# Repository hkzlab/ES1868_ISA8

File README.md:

# ES1868F 8bit ISA Sound Card

## Introduction

This is a sound card for the ISA 8bit bus sporting the **ES1868F** chip by *ESS Technology*.

This chip provides **Sound Blaster PRO 2.0** (stereo), **OPL3** compatibility (via *ESFM*), MPU-401 support and is considered one of the [best chips](https://www.philscomputerlab.com/ess-audiodrive-es1868.html) used in clone cards.

This board provides the following connections:

* Speaker out (amplified)
* Line out
* Line in
* AUX in (internal header, since rev 1.2)
* Microphone in (internal header)
* Joystick port
* MIDI on Joystick port
* Wavetable header
* Volume control header

### Disclaimer

I take NO responsibility for what happens if you decide to build and use this card. Your computer might crash, catch fire or be destroyed in other nasty ways.
You're encourauged to take what you deem fit from this, and use it in your projects!

### Functionalities

✅ means I tested the functionality and it works, ❌ means I tested the functionality and found issues, ? means that the functionality has yet to be tested.

* [✅] FM Synthesis via OPL3 clone (**ESFM**)
* [✅] Digital audio playback
* [✅] Stereo (left/right channel) check (Tested with Sound Blaster PRO Test program, digitized sound mode)
* [✅] Joystick port
* [✅] Speaker Out (amplified)
* [✅] Line out
* [✅] Line in
* [✅] AUX In
* [?] Microphone in
* [✅] MIDI output via Joystick port (tested using DOSMID MPU mode on a Roland SC55)
* [✅] Wavetable daughterboard

The card was tested on:

* [✅] 286 16Mhz / DOS 6.22
* [✅] NEC V20 9.54Mhz / DOS 6.22 (Use **UNISOUND**, see **Configuration** section below)
* [✅] NEC V20 4.77Mhz / DOS 6.22 (Use **UNISOUND**, see **Configuration** section below)
* [✅] 8088 8Mhz / DOS 6.22 (Use **UNISOUND**, see **Configuration** section below)
* [✅] 8088 4.77Mhz / DOS 6.22 (Use **UNISOUND**, see **Configuration** section below)
* [✅] 486DX 40Mhz / DOS 7.1 (Use **UNISOUND**, see **Configuration** section below)
* [✅] Am5x86 40/160Mhz / DOS 7.1 (Use **UNISOUND**, see **Configuration** section below)

## Configuration

This card is jumperless and must be configured before use.
Under DOS you can us the [ESSCFG](software/ESSCFG.EXE) tool and tweak the volume via [ESSVOL](software/ESSVOL.EXE).

The **recommended** way to do this (especially under a very slow machine, like a V20/8088) is by using the [UNISOUND](https://www.vogons.org/viewtopic.php?f=62&t=72553) configurator.

It's important to add the `/XEA` parameter to `UNISOUND.COM` when using it, and remember to execute it after setting the `BLASTER` environment variable, for example with the command `SET BLASTER=A220 I5 D1 P330 T5 J201` (clearly changing the parameters depending on your setup).

**WARNING**: If you use an XT-IDE adapter at the default base address (300h), remember to set the MPU-401 base for this card to something else (like 330h)!

## Bill of Materials

**TODO**

Value of L1/L2/L3 ferrite beads is non critical. I used [these](https://www.mouser.it/ProductDetail/623-2743001112LF).

## Known Issues

### Rev 1.0

* Joystick plug "J3" silkscreen overlaps with some resistors (fixed in 1.1).
* The thread in the audio jacks I'm using (Kycon STX-3100-3CB) is flush with the bracket, so if the bracket has some bending, the plug risks to be pushed away (fixed in 1.1 by moving the connectors 0,5mm towards the edge).

## Credits

Thanks to [Sergey Kiselev](https://github.com/skiselev) for his symbol/footprint library!

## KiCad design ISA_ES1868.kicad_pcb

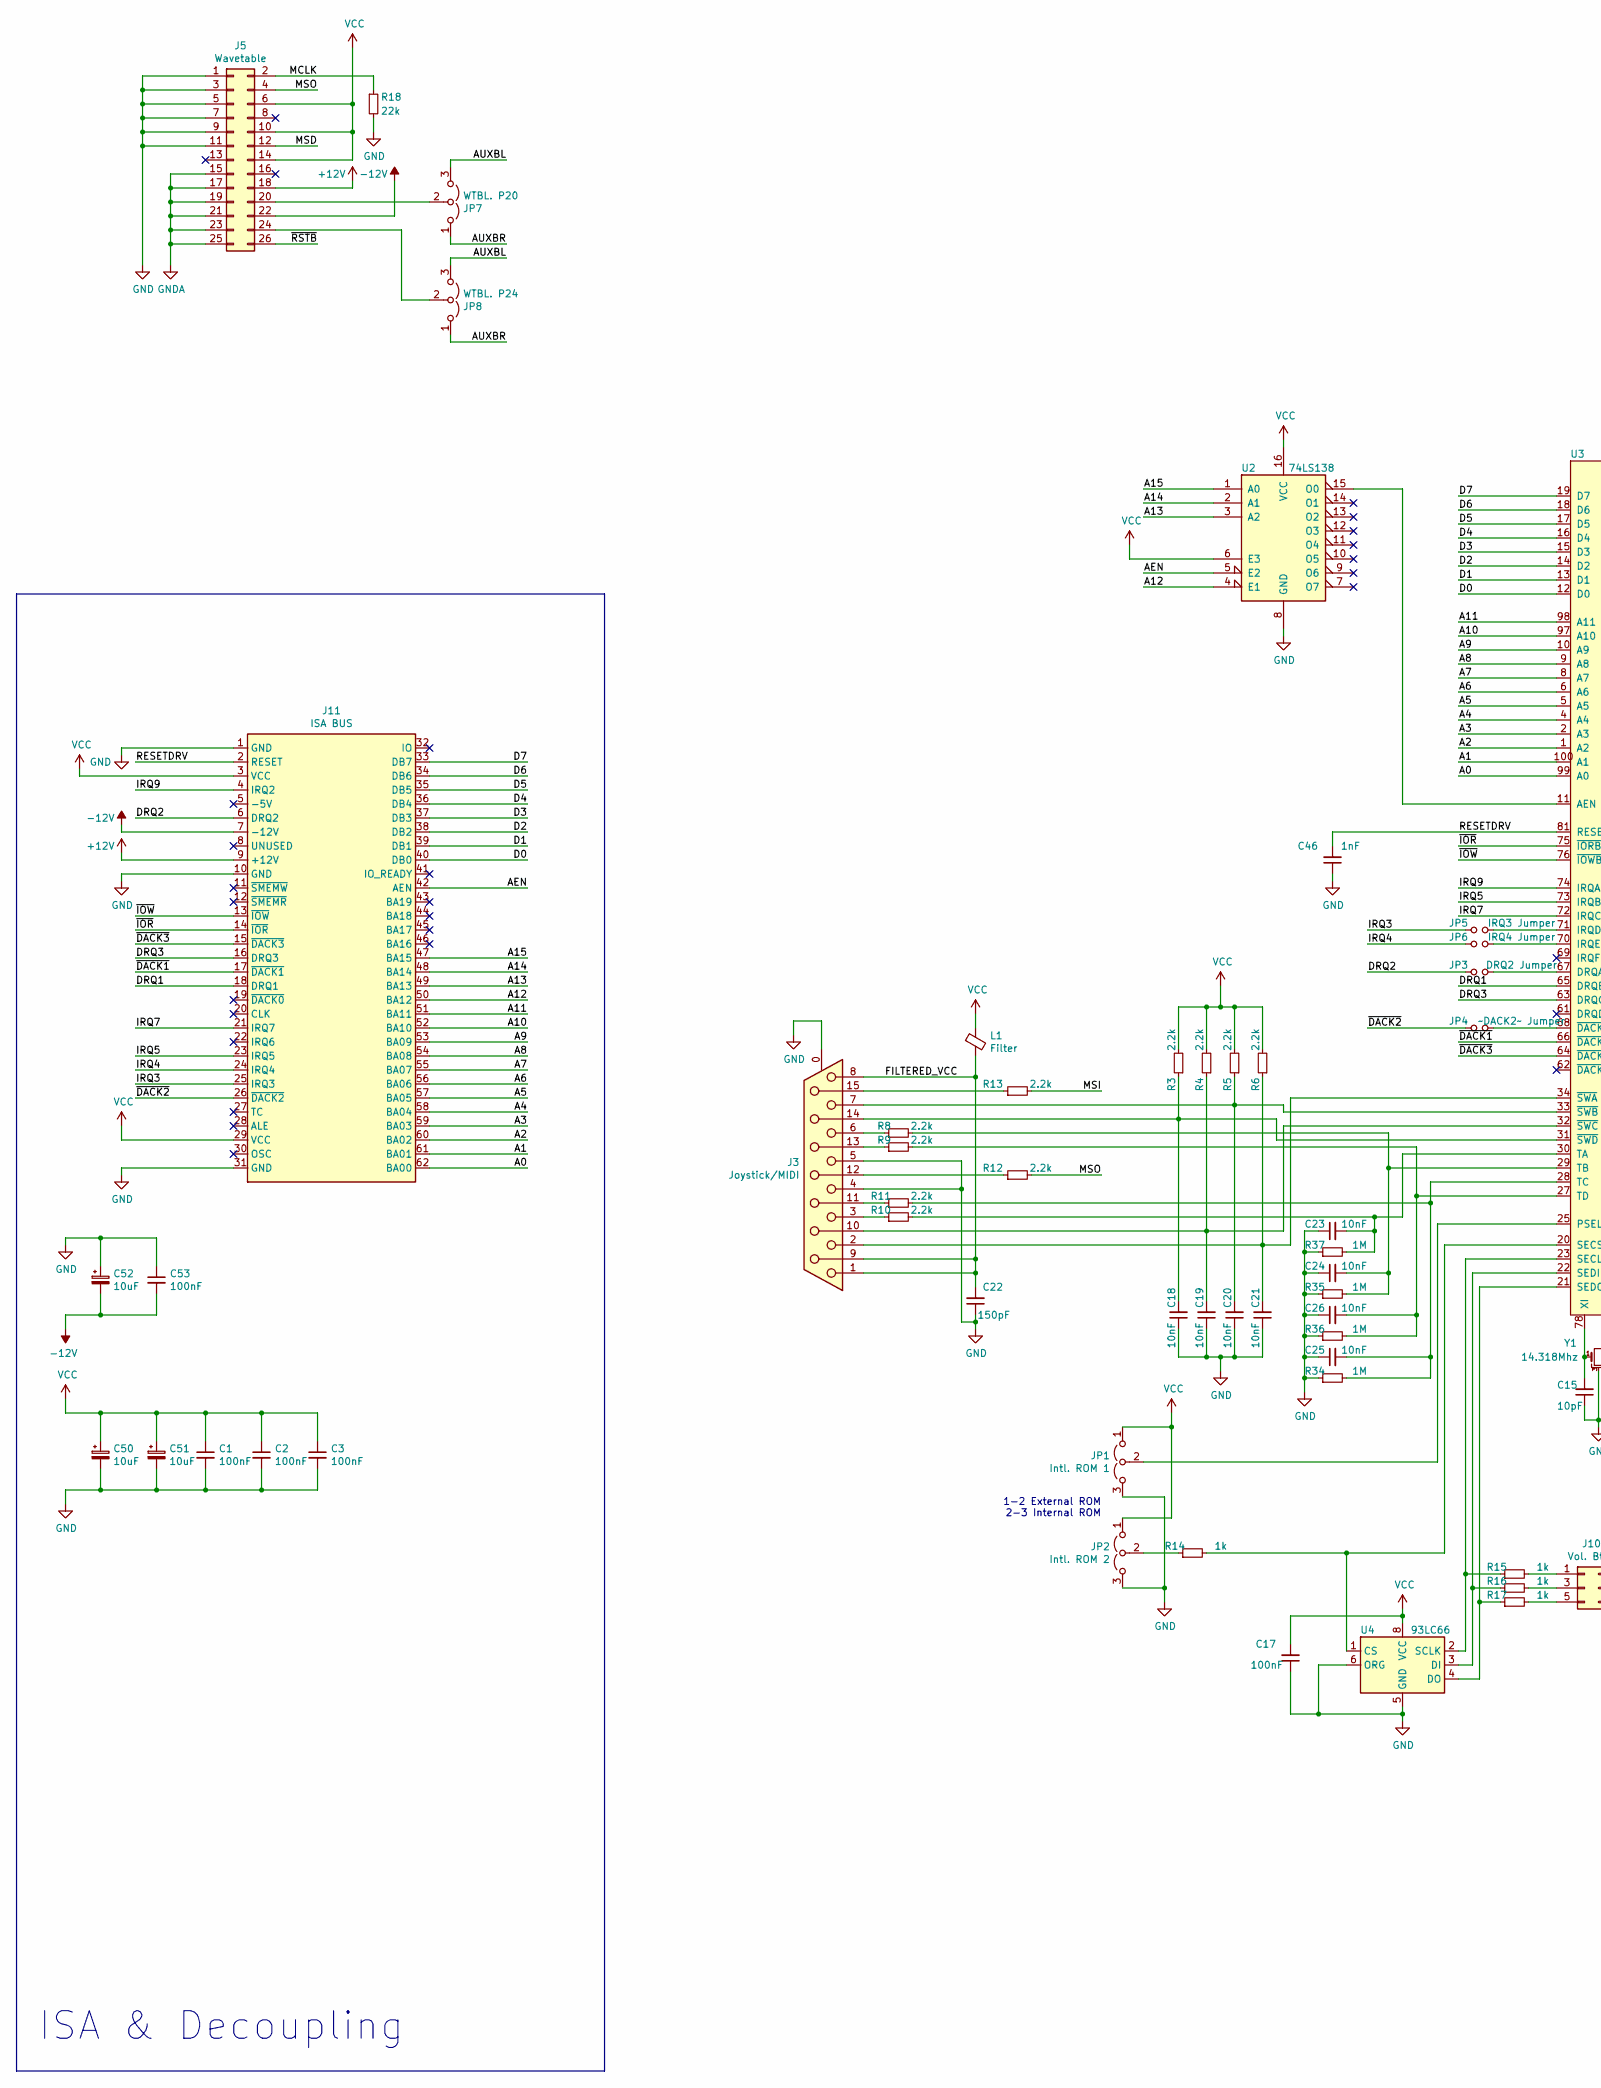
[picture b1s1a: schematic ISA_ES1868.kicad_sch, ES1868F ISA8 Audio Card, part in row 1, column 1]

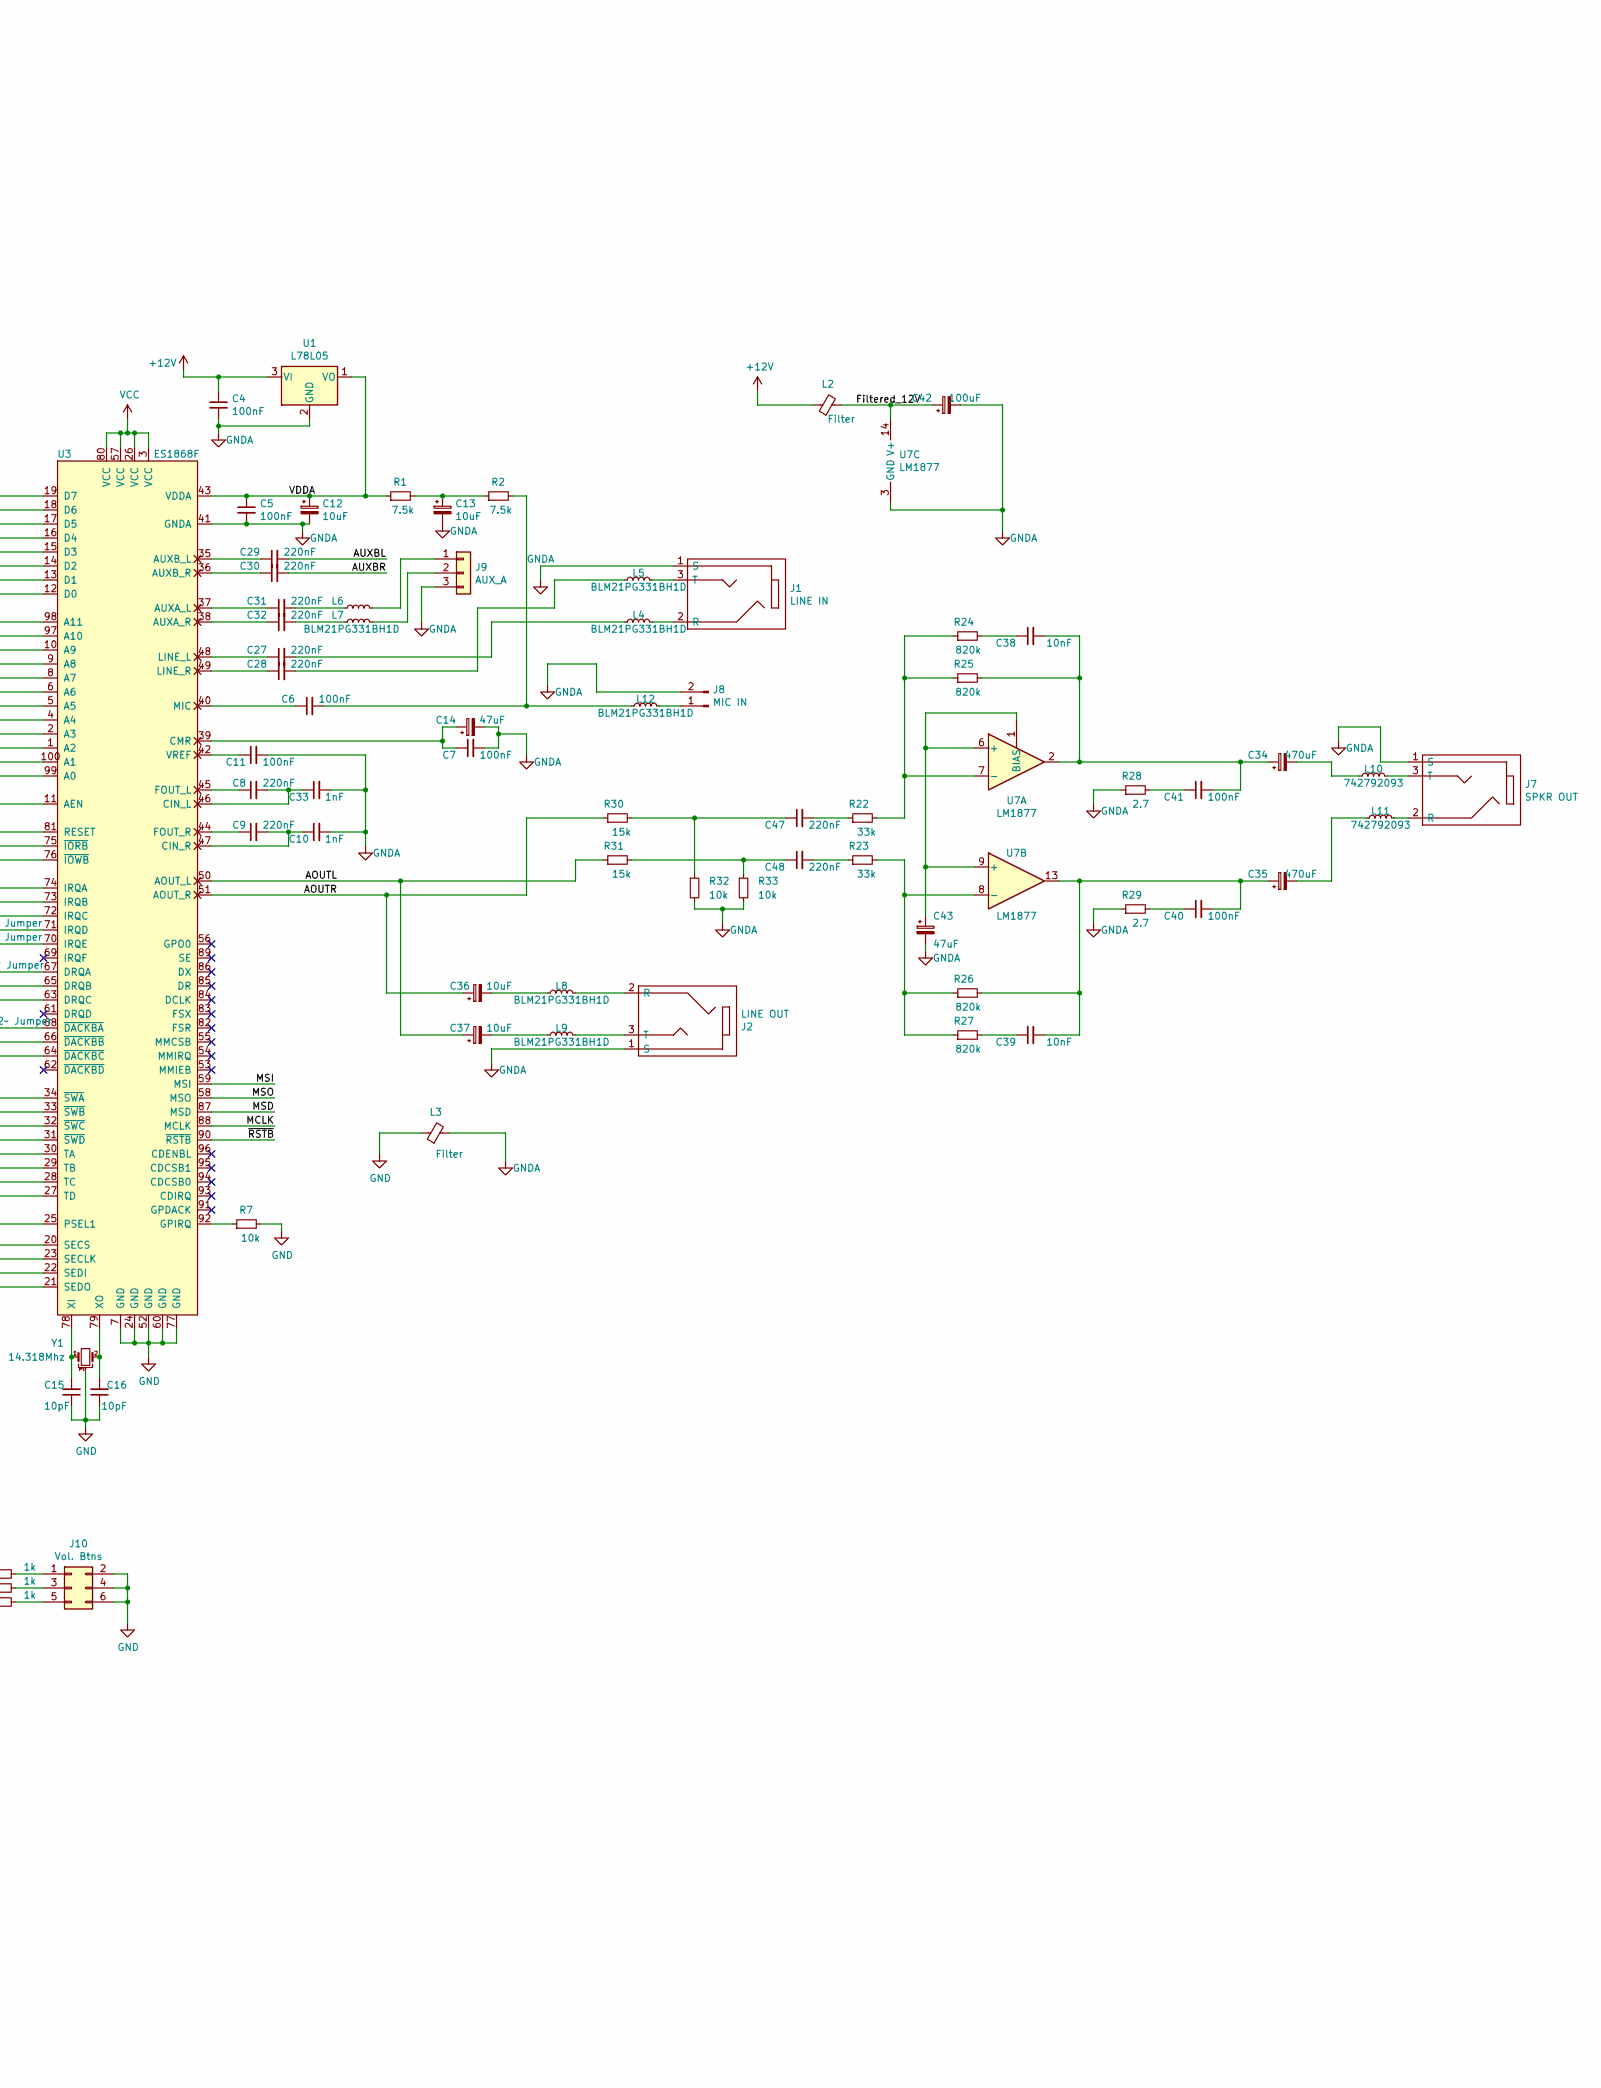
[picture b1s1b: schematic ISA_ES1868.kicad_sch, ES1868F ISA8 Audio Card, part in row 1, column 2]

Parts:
C1, C2, C3, C4, C5, C6, C7, C11, C17, C40, C41, C53: 100nF; C_Disc_D6.0mm_W2.5mm_P5.00mm
C8, C9, C27, C28, C29, C30, C31, C32, C47, C48: 220nF; C_Disc_D6.0mm_W2.5mm_P5.00mm
C10, C33, C46: 1nF; C_Disc_D6.0mm_W2.5mm_P5.00mm
C12, C13, C36, C37, C50, C51, C52: 10uF; CP_Radial_D5.0mm_P2.50mm
C14, C43: 47uF; CP_Radial_D5.0mm_P2.50mm
C15, C16: 10pF; C_Disc_D3.8mm_W2.6mm_P2.50mm
C18, C19, C20, C21, C23, C24, C25, C26, C38, C39: 10nF; C_Disc_D6.0mm_W2.5mm_P5.00mm
C22: 150pF; C_Disc_D6.0mm_W2.5mm_P5.00mm
C34, C35: 470uF; CP_Radial_D8.0mm_P3.50mm
C42: 100uF; CP_Radial_D5.0mm_P2.50mm
J1: LINE IN; Conn_Audio_3.5mm_Stereo_SJ1-352XNG
J2: LINE OUT; Conn_Audio_3.5mm_Stereo_SJ1-352XNG
J3: Joystick/MIDI; SB_DB15_152-3415
J5: Wavetable; PinHeader_2x13_P2.54mm_Vertical
J7: SPKR OUT; Conn_Audio_3.5mm_Stereo_SJ1-352XNG
J8: MIC IN; PinHeader_1x02_P2.54mm_Horizontal
J9: AUX_A; PinHeader_1x03_P2.54mm_Vertical
J10: Vol. Btns; PinHeader_2x03_P2.54mm_Vertical
J11: ISA BUS; Conn_Edge_PCB_ISA8
JP1: Intl. ROM 1; SolderJumper-3_P1.3mm_Open_RoundedPad1.0x1.5mm_NumberLabels
JP2: Intl. ROM 2; SolderJumper-3_P1.3mm_Open_RoundedPad1.0x1.5mm_NumberLabels
JP3: DRQ2 Jumper; SolderJumper-2_P1.3mm_Open_RoundedPad1.0x1.5mm
JP4: ~DACK2~ Jumper; SolderJumper-2_P1.3mm_Open_RoundedPad1.0x1.5mm
JP5: IRQ3 Jumper; SolderJumper-2_P1.3mm_Open_RoundedPad1.0x1.5mm
JP6: IRQ4 Jumper; SolderJumper-2_P1.3mm_Open_RoundedPad1.0x1.5mm
JP7: WTBL. P20; SolderJumper-3_P1.3mm_Open_RoundedPad1.0x1.5mm_NumberLabels
JP8: WTBL. P24; SolderJumper-3_P1.3mm_Open_RoundedPad1.0x1.5mm_NumberLabels
L1, L2, L3: Filter; L_Axial_L5.3mm_D2.2mm_P7.62mm_Horizontal_Vishay_IM-1
L4, L5, L6, L7, L8, L9, L12: BLM21PG331BH1D; L_0805_2012Metric_Pad1.15x1.40mm_HandSolder
L10, L11: 742792093; L_0805_2012Metric_Pad1.15x1.40mm_HandSolder
R1, R2: 7.5k; R_Axial_DIN0207_L6.3mm_D2.5mm_P7.62mm_Horizontal
R3, R4, R5, R6, R8, R9, R10, R11, R12, R13: 2.2k; R_Axial_DIN0207_L6.3mm_D2.5mm_P7.62mm_Horizontal
R7, R32, R33: 10k; R_Axial_DIN0207_L6.3mm_D2.5mm_P7.62mm_Horizontal
R14, R15, R16, R17: 1k; R_Axial_DIN0207_L6.3mm_D2.5mm_P7.62mm_Horizontal
R18: 22k; R_Axial_DIN0207_L6.3mm_D2.5mm_P7.62mm_Horizontal
R22, R23: 33k; R_Axial_DIN0207_L6.3mm_D2.5mm_P7.62mm_Horizontal
R24, R25, R26, R27: 820k; R_Axial_DIN0207_L6.3mm_D2.5mm_P7.62mm_Horizontal
R28, R29: 2.7; R_Axial_DIN0207_L6.3mm_D2.5mm_P7.62mm_Horizontal
R30, R31: 15k; R_Axial_DIN0207_L6.3mm_D2.5mm_P7.62mm_Horizontal
R34, R35, R36, R37: 1M; R_Axial_DIN0207_L6.3mm_D2.5mm_P7.62mm_Horizontal
U1: L78L05; TO-92_Inline
U2: 74LS138; DIP-16_W7.62mm_LongPads
U3: ES1868F; LQFP-14x20mm_P0.5mm
U4: 93LC66; DIP-8_W7.62mm_LongPads
U7: LM1877; DIP-14_W7.62mm_LongPads
Y1: 14.318Mhz; Crystal_HC49-U_Horizontal_1EP_style2

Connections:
+12V: C4.1, J5.18, J11.9 (+12V), L2.1, U1.3 (VI)
-12V: C52.2, C53.2, J5.22, J11.7 (-12V)
/A0: J11.62 (BA00), U3.99 (A0)
/A1: J11.61 (BA01), U3.100 (A1)
/A2: J11.60 (BA02), U3.1 (A2)
/A3: J11.59 (BA03), U3.2 (A3)
/A4: J11.58 (BA04), U3.4 (A4)
/A5: J11.57 (BA05), U3.5 (A5)
/A6: J11.56 (BA06), U3.6 (A6)
/A7: J11.55 (BA07), U3.8 (A7)
/A8: J11.54 (BA08), U3.9 (A8)
/A9: J11.53 (BA09), U3.10 (A9)
/A10: J11.52 (BA10), U3.97 (A10)
/A11: J11.51 (BA11), U3.98 (A11)
/A12: J11.50 (BA12), U2.4 (E1)
/A13: J11.49 (BA13), U2.3 (A2)
/A14: J11.48 (BA14), U2.2 (A1)
/A15: J11.47 (BA15), U2.1 (A0)
/AEN: J11.42 (AEN), U2.5 (E2)
/AOUTL: C37.1, R31.1, U3.50 (AOUT_L)
/AOUTR: C36.1, R30.1, U3.51 (AOUT_R)
/AUXBL: C29.2, JP7.3 (B), JP8.3 (B)
/AUXBR: C30.2, JP7.1 (A), JP8.1 (A)
/D0: J11.40 (DB0), U3.12 (D0)
/D1: J11.39 (DB1), U3.13 (D1)
/D2: J11.38 (DB2), U3.14 (D2)
/D3: J11.37 (DB3), U3.15 (D3)
/D4: J11.36 (DB4), U3.16 (D4)
/D5: J11.35 (DB5), U3.17 (D5)
/D6: J11.34 (DB6), U3.18 (D6)
/D7: J11.33 (DB7), U3.19 (D7)
/DRQ1: J11.18 (DRQ1), U3.65 (DRQB)
/DRQ2: J11.6 (DRQ2), JP3.1
/DRQ3: J11.16 (DRQ3), U3.63 (DRQC)
/FILTERED_VCC: C22.2, J3.1, J3.8, J3.9, L1.2
/Filtered_12V: C42.1, L2.2, U7.14 (V+)
/IRQ3: J11.25 (IRQ3), JP5.1
/IRQ4: J11.24 (IRQ4), JP6.1
/IRQ5: J11.23 (IRQ5), U3.73 (IRQB)
/IRQ7: J11.21 (IRQ7), U3.72 (IRQC)
/IRQ9: J11.4 (IRQ2), U3.74 (IRQA)
/MCLK: J5.2, R18.1, U3.88 (MCLK)
/MSD: J5.12, U3.87 (MSD)
/MSI: R13.2, U3.59 (MSI)
/MSO: J5.4, R12.2, U3.58 (MSO)
/RESETDRV: C46.2, J11.2 (RESET), U3.81 (RESET)
/VDDA: C5.1, C12.1, R1.1, U1.1 (VO), U3.43 (VDDA)
/~DACK1: J11.17 (~DACK1), U3.66 (~DACKBB)
/~DACK2: J11.26 (~DACK2), JP4.1
/~DACK3: J11.15 (~DACK3), U3.64 (~DACKBC)
/~IOR: J11.14 (~IOR), U3.75 (~IORB)
/~IOW: J11.13 (~IOW), U3.76 (~IOWB)
/~RSTB: J5.26, U3.90 (~RSTB)
GND: C1.2, C2.2, C3.2, C15.1, C16.1, C17.1, C18.1, C19.1, C20.1, C21.1, C22.1, C23.1, C24.1, C25.1, C26.1, C46.1, C50.2, C51.2, C52.1, C53.1, J3.0 (PAD), J3.4, J3.5, J5.1, J5.3, J5.5, J5.7, J5.9, J5.11, J10.2, J10.4, J10.6, J11.1 (GND), J11.10 (GND), J11.31 (GND), JP1.3 (B), JP2.3 (B), L3.1, R7.2, R18.2, R34.1, R35.1, R36.1, R37.1, U2.8 (GND), U3.7 (GND), U3.24 (GND), U3.52 (GND), U3.60 (GND), U3.77 (GND), U4.5 (GND), U4.6 (ORG), Y1.3
GNDA: C4.2, C5.2, C7.2, C10.2, C11.2, C12.2, C13.2, C14.2, C33.2, C42.2, C43.2, J1.1 (S), J2.1 (S), J5.15, J5.17, J5.19, J5.21, J5.23, J5.25, J7.1 (S), J8.2, J9.3, L3.2, R28.1, R29.1, R32.2, R33.2, U1.2 (GND), U3.41 (GNDA), U7.3 (GND), U7.4 (GND), U7.5 (GND), U7.10 (GND), U7.11 (GND), U7.12 (GND)
unnamed: C6.1, U3.40 (MIC)
unnamed: C6.2, L12.2, R2.2
unnamed: C8.1, U3.45 (FOUT_L)
unnamed: C9.1, U3.44 (FOUT_R)
unnamed: C9.2, C10.1, U3.47 (CIN_R)
unnamed: C11.1, U3.42 (VREF)
unnamed: C13.1, R1.2, R2.1
unnamed: C7.1, C14.1, U3.39 (CMR)
unnamed: C15.2, U3.78 (XI), Y1.1
unnamed: C16.2, U3.79 (XO), Y1.2
unnamed: C18.2, J3.14, R3.1, U3.31 (~SWD)
unnamed: C19.2, J3.10, R4.1, U3.32 (~SWC)
unnamed: C20.2, J3.7, R5.1, U3.33 (~SWB)
unnamed: C21.2, J3.2, R6.1, U3.34 (~SWA)
unnamed: C23.2, R10.2, R37.2, U3.30 (TA)
unnamed: C24.2, R8.2, R35.2, U3.29 (TB)
unnamed: C25.2, R11.2, R34.2, U3.28 (TC)
unnamed: C26.2, R9.2, R36.2, U3.27 (TD)
unnamed: C27.1, U3.48 (LINE_L)
unnamed: C27.2, L4.2
unnamed: C28.1, U3.49 (LINE_R)
unnamed: C28.2, L5.2
unnamed: C29.1, U3.35 (AUXB_L)
unnamed: C30.1, U3.36 (AUXB_R)
unnamed: C31.1, U3.37 (AUXA_L)
unnamed: C31.2, L6.2
unnamed: C32.1, U3.38 (AUXA_R)
unnamed: C32.2, L7.2
unnamed: C8.2, C33.1, U3.46 (CIN_L)
unnamed: C34.1, C38.2, C41.2, R25.2, U7.2
unnamed: C34.2, L10.2
unnamed: C35.1, C39.2, C40.2, R26.2, U7.13
unnamed: C35.2, L11.2
unnamed: C36.2, L8.2
unnamed: C37.2, L9.2
unnamed: C38.1, R24.2
unnamed: C39.1, R27.2
unnamed: C40.1, R29.2
unnamed: C41.1, R28.2
unnamed: C43.1, U7.1 (BIAS), U7.6 (+), U7.9 (+)
unnamed: C47.1, R30.2, R32.1
unnamed: C47.2, R22.1
unnamed: C48.1, R31.2, R33.1
unnamed: C48.2, R23.1
unnamed: J1.2 (R), L4.1
unnamed: J1.3 (T), L5.1
unnamed: J2.2 (R), L8.1
unnamed: J2.3 (T), L9.1
unnamed: J3.3, R10.1
unnamed: J3.6, R8.1
unnamed: J3.11 (P111), R11.1
unnamed: J3.12, R12.1
unnamed: J3.13, R9.1
unnamed: J3.15, R13.1
unnamed: J5.20, JP7.2 (C)
unnamed: J5.24, JP8.2 (C)
unnamed: J7.2 (R), L11.1
unnamed: J7.3 (T), L10.1
unnamed: J8.1, L12.1
unnamed: J9.1, L6.1
unnamed: J9.2, L7.1
unnamed: J10.1, R15.2
unnamed: J10.3, R16.2
unnamed: J10.5, R17.2
unnamed: JP1.2 (C), U3.25 (PSEL1)
unnamed: JP2.2 (C), R14.1
unnamed: JP3.2, U3.67 (DRQA)
unnamed: JP4.2, U3.68 (~DACKBA)
unnamed: JP5.2, U3.71 (IRQD)
unnamed: JP6.2, U3.70 (IRQE)
unnamed: R7.1, U3.92 (GPIRQ)
unnamed: R14.2, U3.20 (SECS), U4.1 (CS)
unnamed: R15.1, U3.23 (SECLK), U4.2 (SCLK)
unnamed: R16.1, U3.22 (SEDI), U4.3 (DI)
unnamed: R17.1, U3.21 (SEDO), U4.4 (DO)
unnamed: R22.2, R24.1, R25.1, U7.7 (-)
unnamed: R23.2, R26.1, R27.1, U7.8 (-)
unnamed: U2.15 (O0), U3.11 (AEN)
VCC: C1.1, C2.1, C3.1, C17.2, C50.1, C51.1, J5.6, J5.10, J5.14, J11.3 (VCC), J11.29 (VCC), JP1.1 (A), JP2.1 (A), L1.1, R3.2, R4.2, R5.2, R6.2, U2.6 (E3), U2.16 (VCC), U3.3 (VCC), U3.26 (VCC), U3.57 (VCC), U3.80 (VCC), U4.8 (VCC)

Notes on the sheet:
ISA & Decoupling
1-2 External ROM 2-3 Internal ROM

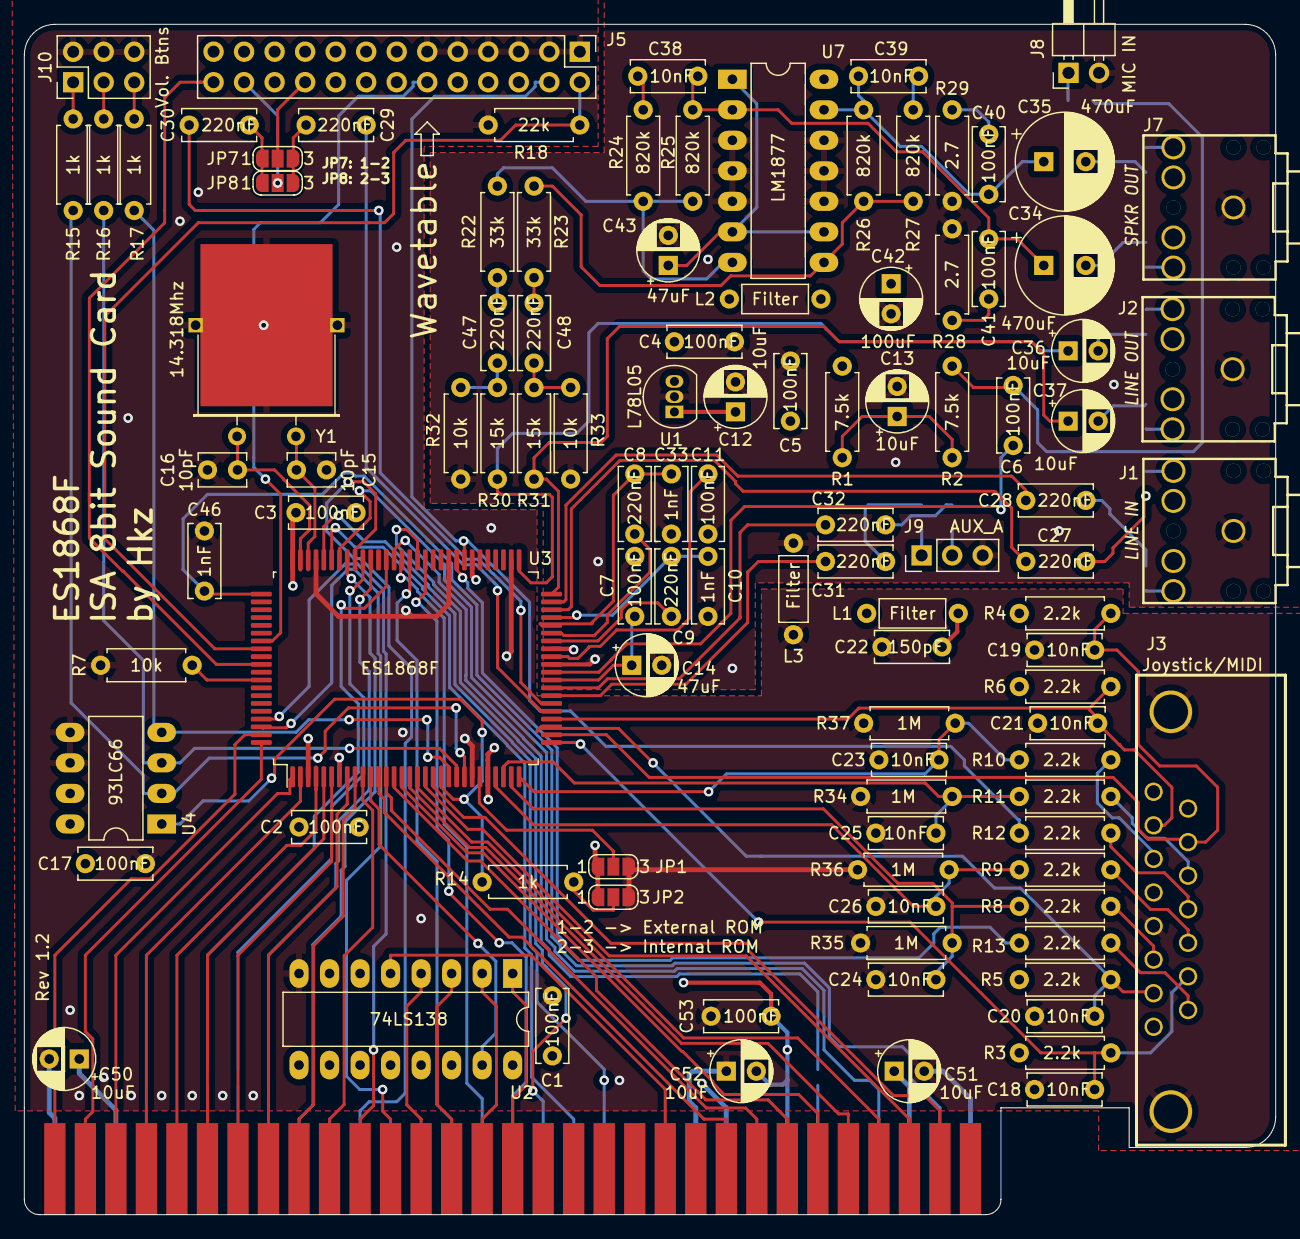
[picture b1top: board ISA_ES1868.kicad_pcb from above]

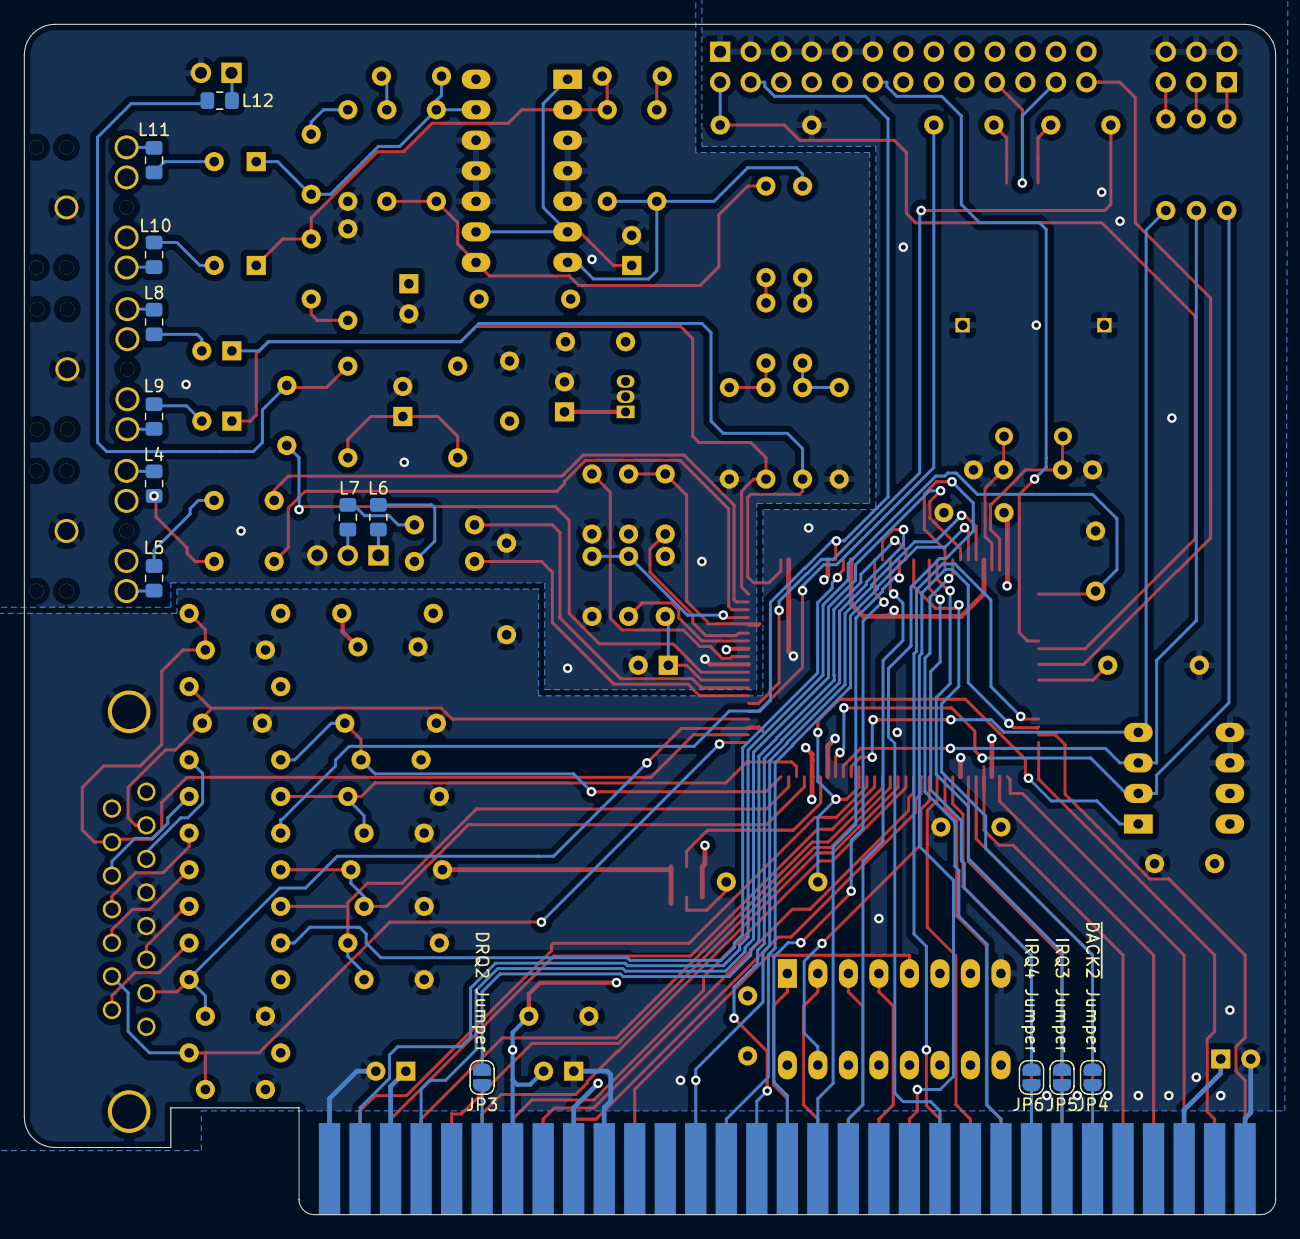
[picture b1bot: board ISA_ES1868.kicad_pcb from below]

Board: 4 copper layers, 104.1 x 99.1 mm, 119 parts (13 on the bottom side), 134 nets.

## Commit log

2021-05-07 Add empty project
2021-05-07 Add document describing example board from ESS
2021-05-07 Begin creating the ES1868F symbol
2021-05-07 More pins to ES1868F symbol
2021-05-07 More pins for ES1868
2021-05-07 More pins
2021-05-07 Add some docs for wavetable
2021-05-07 Add QFP footprint
2021-05-07 begin shaping the ES1868F symbol
2021-05-07 Completed ES1868 symbol
2021-05-08 Remove some unused connections from edge
2021-05-08 Begin drawing schematic
2021-05-08 More schematics
2021-05-08 Copy over more of the schematics for the audio chip
2021-05-08 Partial schematic for ESS chip done
2021-05-09 Completed the schematics
2021-05-09 Complete schematic
2021-05-09 Complete schematics, assigned footprints
2021-05-09 Change some output options
2021-05-09 start organizing things on the PCB
2021-05-09 More placement on PCB
2021-05-09 Organize external connectors
2021-05-10 Begin organizing PCB
2021-05-10 More board component placement
2021-05-10 Routed audio traces
2021-05-10 Basic power routing
2021-05-10 Commit pre-autoroute
2021-05-10 Routed
2021-05-10 Changed some routing
2021-05-10 Change silkscreen
2021-05-10 More vias for a better ground plane
2021-05-10 More silkscreen adjustments
2021-05-10 Add description test
2021-05-11 Mark some unconnected pins as unconnected
2021-05-11 Fix some traces and copper areas
2021-05-11 Redo copper fills
2021-05-11 Reroute some traces
2021-05-11 Last changes to PCB
2021-05-13 Add amplifier doc
2021-05-14 Use put line out on jack
2021-05-14 Move a gnd trace
2021-05-14 Update some traces on PCB
2021-05-14 Updated PCB
2021-05-14 Moved some components on PCB
2021-05-14 Update the PCB
2021-05-14 Fixed silkscreen text
2021-05-15 changed analog ground zone
2021-05-18 Update silkscreen
2021-05-19 Add eeprom dump and notes
2021-05-19 Add drivers, notes and PnP EEPROM dump
2021-05-19 Reorganized crystal on board and moved some traces
2021-05-19 Slight change to traces, add gerbers
2021-05-19 Changes to gnd plane, redone gerbers
2021-05-19 Add more gnd plane, redone gerbers
2021-05-20 Rerouting some traces
2021-05-20 Rework some traces
2021-05-20 More traces rework
2021-05-22 Moved some silkscreen
2021-05-22 Keep L/R audio traces on different sides of the board
2021-05-23 Add keystone bracket footprint from snark-barker
2021-05-23 Begin adding shape for bracket cutout, moved trace
2021-05-23 Move phone plugs a bit towards the edge
2021-05-23 Add bracket model
2021-05-23 Move some of the silkscreen
2021-05-23 Add SB DB15 connector
2021-05-23 Refill board, move some measurements
2021-05-23 Rerouted and resized some traces
2021-05-24 Move some components on the bracket
2021-05-24 Updated gerbers
2021-05-24 Add 9204-1 bracket doc
2021-05-24 Add keystone 9204-1
2021-05-24 Mirror some components of the keystone bracket
2021-05-24 Update the footprint
2021-05-24 Move silkscreen item
2021-05-24 Slightly move a component
2021-05-24 Update gerbers
2021-05-24 Add 9200-3 bracket
2021-05-24 Move connectors to use 9200-3 bracket
2021-05-24 Moved connector again
2021-05-24 Redo joystick connections again
2021-05-24 move some traces, redo gerbers
2021-05-25 Fixed a footprint, added eth footprint
2021-05-25 Add another bracket
2021-05-25 Additional measurements
2021-05-25 Add another keystone bracket
2021-05-25 Add selection to invert channels from wavetable
2021-05-26 Replace 2 ceramic caps with electrolitic
2021-05-26 Better ground plane, redo gerber
2021-05-26 Make 12V trace a bit more hefty
2021-05-29 adjust J3 on silkscreen
2021-06-07 Slight adjustment to silkscreen
2021-06-07 Fix ES1868F unused pin symbol
2021-06-08 Better gnd plane filling
2021-06-08 Updated README, added software
2021-06-08 Add additional notes
2021-06-08 Updated README with additional notes
2021-06-08 add warning
2021-06-08 Wording
2021-06-08 Added some more things to check
2021-06-08 Some more precisations regarding the emulation of SBPro 2
2021-06-08 Remove redundant soft dir
2021-06-08 Additional notes to the README
2021-06-09 Additional data in README
2021-06-09 Add credits
2021-06-09 Add further notes in README
2021-06-09 Further notes on readme
2021-06-12 Move audio jacks 0,5mm towards the edge
2021-06-12 Notes in the README
2021-06-14 Updated README with additional testing
2021-06-17 Fix AEN pin name
2021-06-25 Add rev 1.1 gerbers
2021-07-08 Remove note on basic testing
2021-07-09 Add headers for the aux_a input
2021-07-09 Change some routing
2021-07-10 Add es1869 tech manual
2021-07-10 Add ferrite beads at outputs and inputs, as advised by ES1869 datasheet
2021-07-11 Changed ferrite beads for audio output
2021-07-11 Update PCB with new beads
2021-07-19 Modified schematic for ES1868
2021-07-19 changed inductance type
2021-07-19 Fix the name on the schema sheet
2021-11-09 Update KiCad url
2021-11-12 Further README updates
2021-11-12 Small fix in readme
2022-07-25 Upgrade to KiCad 6
2022-07-25 fix missing 3d models
2023-10-13 Initial import to KiCad 7
2023-10-13 Restore edge clearance
